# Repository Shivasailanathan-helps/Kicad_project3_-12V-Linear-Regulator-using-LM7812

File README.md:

# Kicad_project3_-12V-Linear-Regulator-using-LM7812
This project features the schematic capture and dual-layer PCB layout of a +12V Regulated DC Power Supply, designed in KiCad EDA. The board converts an AC input into a clean, stable +12V DC output suitable for powering sensitive analog/digital electronics and bench prototyping setups.

## Features:
Rectification & Primary Filtering: Full-wave bridge rectifier (D1 to D4) paired with a 1000muF electrolytic capacitor for low-frequency AC ripple suppression.
Linear Voltage Regulation: LM7812 IC (TO-220 package) delivering steady +12V output regulation.
Output Decoupling: Parallel combination of a 470muF electrolytic bulk storage capacitor and a 0.1muF(104) ceramic high-frequency bypass capacitor for transient response and noise filtering.
Visual Status Indication: Onboard status LED D5 with a 1k current-limiting resistor R1.
Dual-Layer Layout Strategy: Utilizes a Top Copper (F.Cu) +12V power pour for component heat sinking alongside a continuous Bottom Copper (B.Cu) Ground (GND) plane for low-impedance return paths and EMI reduction. Surface-mount ground pads are connected directly to the ground plane using plated vias.

## Process:
### Phase 1: Schematic Capture & ERC Verification
1. **Bridge Rectification & Filtering:** Built a full-wave diode bridge (D1-D4) fed by connector $J_1$, filtered by bulk capacitor C1 to smooth AC mains ripple before linear regulation.
2. **Linear Regulation & Decoupling:** Integrated the LM7812 regulator ($U_1$) with parallel output capacitors (C2 for load transient recovery, C3 for high-frequency noise attenuation).
3. **ERC & `PWR_FLAG` Configuration:** Resolved KiCad "undriven power pin" Electrical Rules Check errors by adding `PWR_FLAG` symbols to both the positive rectified rail and Ground node. This tells KiCad's static pin-checking engine that power enters the net via passive components (J1, diodes).
4. **Netlist Junction Repair:** Diagnosed an issue where return pads were assigned an auto-generated net name (`Net-(D3-A)`) rather than `GND`. Located a missing junction dot on the schematic where LM7812 Pin 2 intersected the main return rail. Re-establishing the junction node restored full netlist integrity across all return pads.

---

### Phase 2: PCB Layout & Copper Pour Strategy
1. **Board Boundary Definition:** Defined a closed PCB perimeter on the **`Edge.Cuts`** layer to establish the physical board outline and enable shaded area rendering.
2. **Bottom-Layer Ground Plane (`B.Cu`):** Flooded the bottom copper layer with a solid **`GND`** zone. Through-hole component pins automatically tied into this continuous $0\text{V}$ reference plane via thermal relief spokes.
3. **Top-Layer Power Plane (`F.Cu`):** Poured a **`+12V`** copper zone across the output side of the top layer. This plane acts as a low-impedance power distribution rail while serving as an onboard heat sink for the LM7812 IC.
4. **Via-Stitching for Surface-Mount Pads:** Placed plated vias adjacent to surface-mount (SMD) ground pads (C2, C3, D5), dropping top-layer SMD return paths straight down into the continuous bottom ground plane.

---

### Phase 3: Verification & Inspection
* **3D Visual Audit:** Verified component clearances, mechanical footprint orientations, and solder mask openings in KiCad's 3D Viewer (`Alt + 3`).
* **Net Highlighting:** Conducted net-continuity checks on the `+12V` rail to ensure low-resistance paths from the LM7812 output terminal (`VO`) to the DC terminal block.

## Extras:
### Why the Top Copper (`F.Cu`) Zone Covers Only the Right Half?

The top-layer red copper pour (`F.Cu`) is intentionally restricted to the right half of the board, while the bottom-layer blue ground plane (`B.Cu`) extends across the entire PCB. This design decision is based on three core PCB engineering principles:

#### 1. Power Domain Separation (AC/Raw DC vs. Regulated DC)
* **Left Half (Unregulated / AC Domain):** Contains the AC input connector (J1) and the full-wave bridge rectifier (D1-D4). This region carries alternating current and raw, pulsating DC prior to regulation.
* **Right Half (Regulated DC Domain):** Begins at the output pin (Pin 3) of the LM7812 regulator (U1). 
* **Reason:** The +12V power rail physically does not exist until *after* the linear regulator. Extending a +12V copper plane into the left section would be electrically invalid and risk shorting out distinct AC lines or raw diode nodes.

#### 2. EMI & Noise Isolation
* Diode switching and AC input traces generate localized electromagnetic noise and ripple.
* Restricting the +12V copper pour strictly to the output side prevents AC switching noise from capacitively coupling into the clean, filtered DC output plane.

#### 3. Continuous Bottom Ground Plane (`B.Cu`) Extension
* While the top layer (`F.Cu`) is split into manual traces on the left and a +12V plane on the right, the bottom layer (`B.Cu`) spans the full PCB length.
* This provides a continuous, unbroken 0V ground return path across all circuit stages, minimizing current loop areas, reducing EMI radiation, and acting as a shield for the entire board.

## Outputs:

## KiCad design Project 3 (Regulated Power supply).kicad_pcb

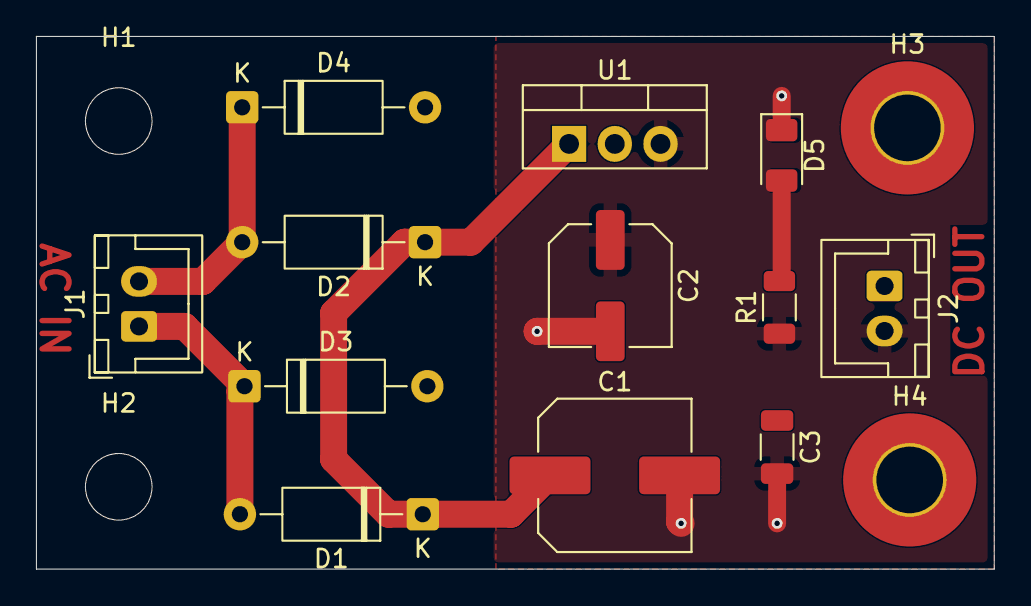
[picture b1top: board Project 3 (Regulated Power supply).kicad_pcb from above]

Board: 2 copper layers, 53.2 x 29.6 mm, 16 parts (0 on the bottom side), 6 nets.

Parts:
C1: 1000uF/25V; C_Elec_8x10.2
C2: 470uF/16V; C_Elec_6.3x7.7
C3: 104; C_1206_3216Metric
D1, D2, D3, D4: D; D_A-405_P10.16mm_Horizontal
D5: LED_Small; LED_1206_3216Metric
H1, H2: MountingHole; MountingHole_3.7mm
H3, H4: MountingHole_Pad; MountingHole_3.7mm_Pad_TopOnly
J1: AC IN; JST_XH_B2B-XH-A_1x02_P2.50mm_Vertical
J2: DC OUT; JST_XH_B2B-XH-A_1x02_P2.50mm_Vertical
R1: 1K; R_1206_3216Metric
U1: LM7812_TO220; TO-220-3_Vertical

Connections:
+12V: C2.1, C3.1, J2.2, R1.1, U1.3 (VO)
GND: C1.2, C2.2, C3.2, D3.2 (A), D4.2 (A), D5.1 (K), H3.1 (1_1), H4.1 (1_1), J2.1, U1.2 (GND)
unnamed: D1.2 (A), D3.1 (K), J1.1
unnamed: C1.1, D1.1 (K), D2.1 (K), U1.1 (VI)
unnamed: D2.2 (A), D4.1 (K), J1.2
unnamed: D5.2 (A), R1.2
